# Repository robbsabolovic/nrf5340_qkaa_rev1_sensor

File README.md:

# nrf5340_qkaa_rev1_sensor
Simple Kicad 6.0 nRF5340 sensor board example

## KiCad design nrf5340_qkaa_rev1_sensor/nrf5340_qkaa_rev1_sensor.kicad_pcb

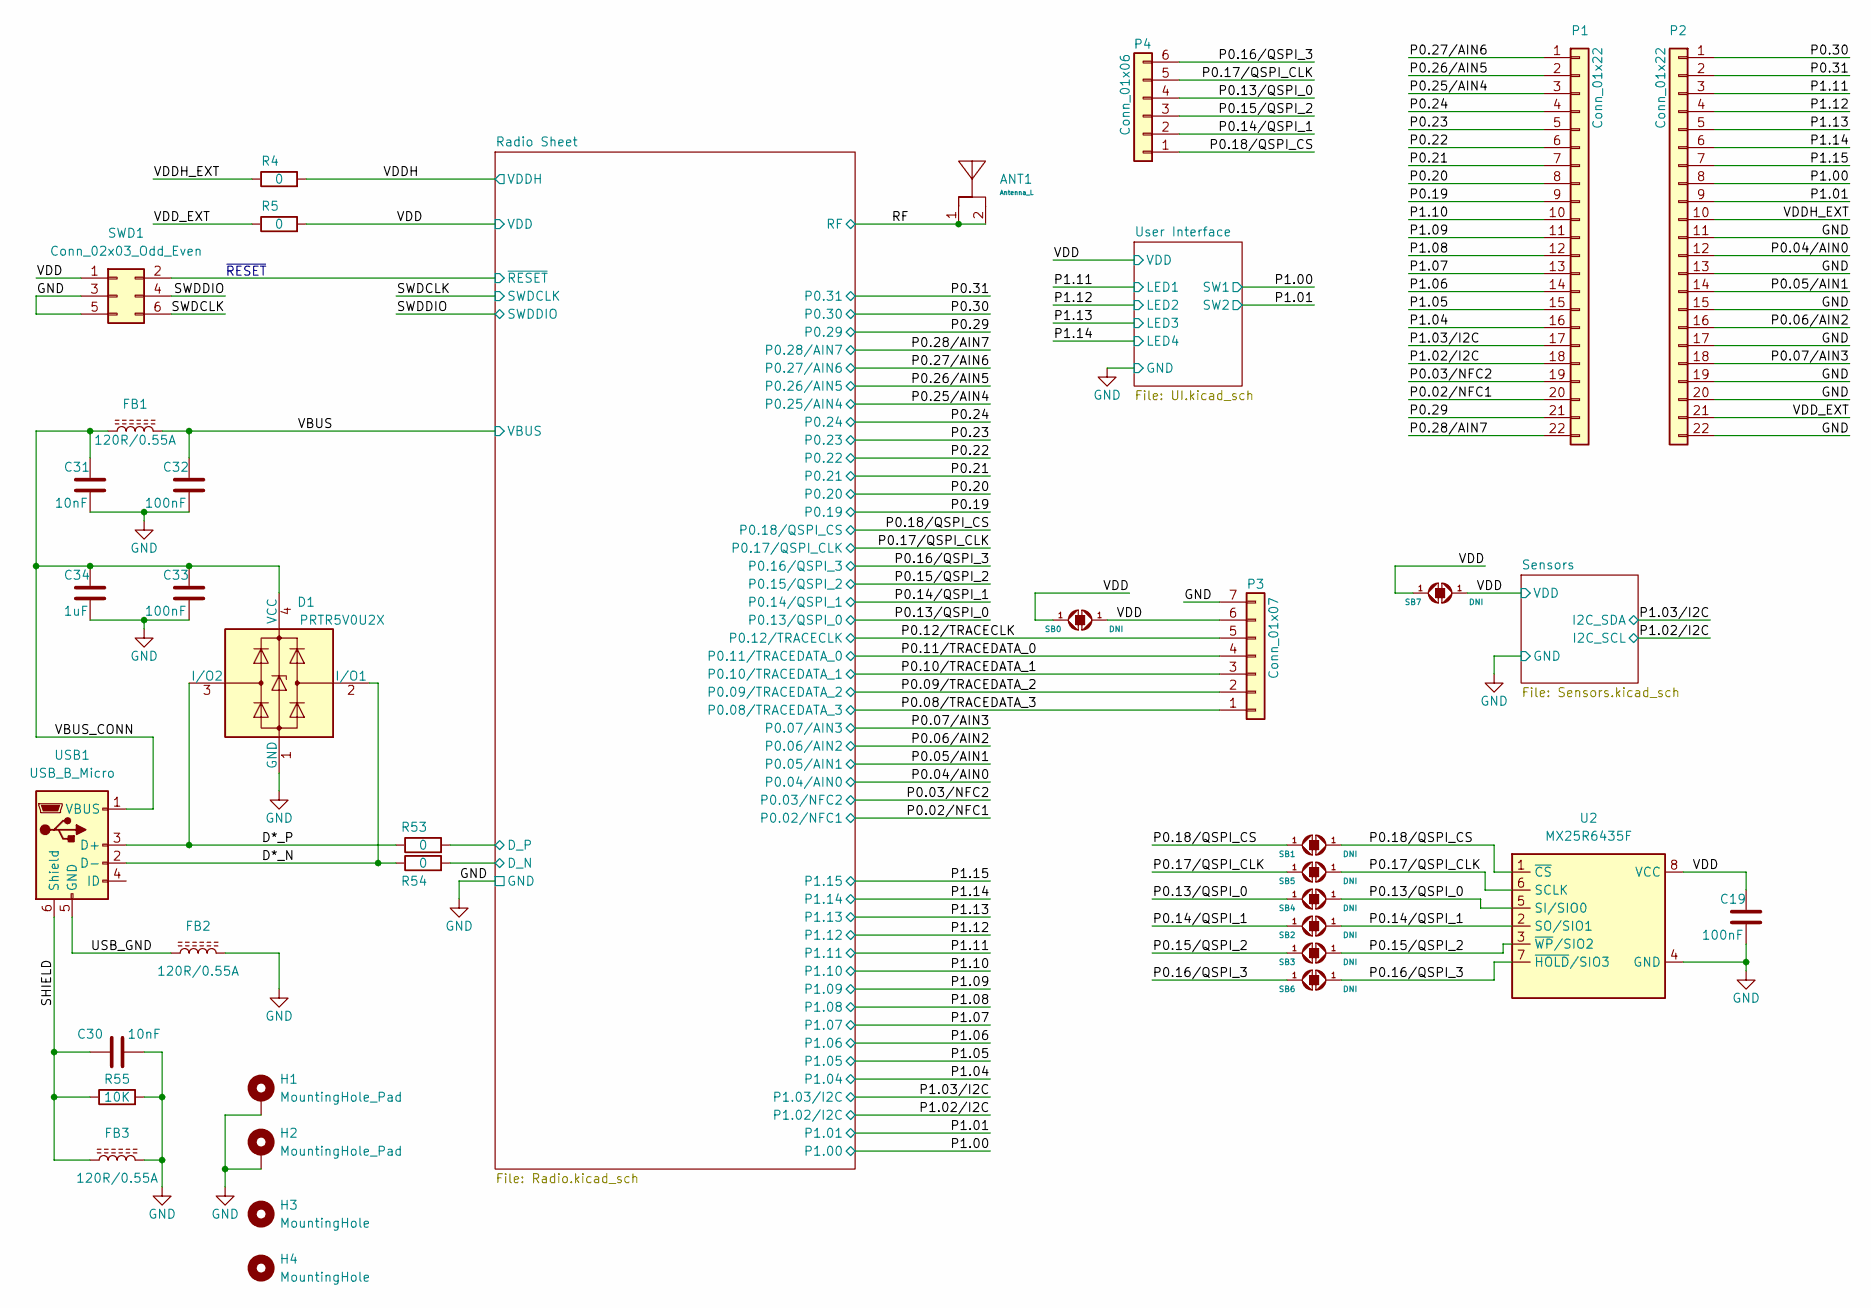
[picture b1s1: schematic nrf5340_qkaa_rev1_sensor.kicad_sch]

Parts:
ANT1: Antenna_L; ANTENNA_L_2_4GHZ
C19, C32, C33: 100nF; C_0201
C30, C31: 10nF; C_0201
C34: 1uF; C_0603
D1: PRTR5V0U2X; SOT-143
FB1, FB2, FB3: 120R/0.55A; FB_0603
H1, H2: MountingHole_Pad; MountingHole_2.5mm_Plated
H3, H4: MountingHole; MountingHole_2.5mm
P1, P2: Conn_01x22; PinHeader_1x022_P2.54mm_Vertical
P3: Conn_01x07; PinHeader_1x07_P2.54mm_Vertical
P4: Conn_01x06; PinHeader_1x06_P2.54mm_Vertical
R4, R5, R53, R54: 0; R_0201
R55: 10K; R_0201
SB0, SB1, SB2, SB3, SB4, SB5, SB6, SB7: DNI; SB_PAD_SHORT
SWD1: Conn_02x03_Odd_Even; TC2030-IDC-NL
U2: MX25R6435F; SOP-8_3.9x4.9mm_P1.27mm
USB1: USB_B_Micro; USB_Micro-B_Amphenol_10103594-0001LF_Horizontal

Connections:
/D*_N: D1.2 (I/O1), R54.1, USB1.2 (D-)
/D*_P: D1.3 (I/O2), R53.1, USB1.3 (D+)
/P0.02/NFC1: P1.20; also elsewhere on the board
/P0.03/NFC2: P1.19; also elsewhere on the board
/P0.04/AIN0: P2.12; also elsewhere on the board
/P0.05/AIN1: P2.14; also elsewhere on the board
/P0.06/AIN2: P2.16; also elsewhere on the board
/P0.07/AIN3: P2.18; also elsewhere on the board
/P0.08/TRACEDATA_3: P3.1; also elsewhere on the board
/P0.09/TRACEDATA_2: P3.2; also elsewhere on the board
/P0.10/TRACEDATA_1: P3.3; also elsewhere on the board
/P0.11/TRACEDATA_0: P3.4; also elsewhere on the board
/P0.12/TRACECLK: P3.5; also elsewhere on the board
/P0.13/QSPI_0: P4.4, SB4.1, U2.5 (SI/SIO0); also elsewhere on the board
/P0.14/QSPI_1: P4.2, SB2.1, U2.2 (SO/SIO1); also elsewhere on the board
/P0.15/QSPI_2: P4.3, SB3.1, U2.3 (~WP/SIO2); also elsewhere on the board
/P0.16/QSPI_3: P4.6, SB6.1, U2.7 (~HOLD/SIO3); also elsewhere on the board
/P0.17/QSPI_CLK: P4.5, SB5.1, U2.6 (SCLK); also elsewhere on the board
/P0.18/QSPI_CS: P4.1, SB1.1, U2.1 (~CS); also elsewhere on the board
/P0.19: P1.9; also elsewhere on the board
/P0.20: P1.8; also elsewhere on the board
/P0.21: P1.7; also elsewhere on the board
/P0.22: P1.6; also elsewhere on the board
/P0.23: P1.5; also elsewhere on the board
/P0.24: P1.4; also elsewhere on the board
/P0.25/AIN4: P1.3; also elsewhere on the board
/P0.26/AIN5: P1.2; also elsewhere on the board
/P0.27/AIN6: P1.1; also elsewhere on the board
/P0.28/AIN7: P1.22; also elsewhere on the board
/P0.29: P1.21; also elsewhere on the board
/P0.30: P2.1; also elsewhere on the board
/P0.31: P2.2; also elsewhere on the board
/P1.00: P2.8; also elsewhere on the board
/P1.01: P2.9; also elsewhere on the board
/P1.02/I2C: P1.18; also elsewhere on the board
/P1.03/I2C: P1.17; also elsewhere on the board
/P1.04: P1.16; also elsewhere on the board
/P1.05: P1.15; also elsewhere on the board
/P1.06: P1.14; also elsewhere on the board
/P1.07: P1.13; also elsewhere on the board
/P1.08: P1.12; also elsewhere on the board
/P1.09: P1.11; also elsewhere on the board
/P1.10: P1.10; also elsewhere on the board
/P1.11: P2.3; also elsewhere on the board
/P1.12: P2.4; also elsewhere on the board
/P1.13: P2.5; also elsewhere on the board
/P1.14: P2.6; also elsewhere on the board
/P1.15: P2.7; also elsewhere on the board
/RF: ANT1.1, ANT1.2; also elsewhere on the board
/Radio Sheet/D_N: R54.2; also elsewhere on the board
/Radio Sheet/D_P: R53.2; also elsewhere on the board
/Radio Sheet/~RESET: SWD1.2; also elsewhere on the board
/SHIELD: C30.1, FB3.1, R55.1, USB1.6 (Shield)
/SWDCLK: SWD1.6; also elsewhere on the board
/SWDDIO: SWD1.4; also elsewhere on the board
/USB_GND: FB2.1, USB1.5 (GND)
/VBUS_CONN: C31.1, C33.1, C34.1, D1.4 (VCC), FB1.1, USB1.1 (VBUS)
/VDDH: R4.2; also elsewhere on the board
/VDDH_EXT: P2.10, R4.1
/VDD_EXT: P2.21, R5.1
GND: C19.2, C30.2, C31.2, C32.2, C33.2, C34.2, D1.1 (GND), FB2.2, FB3.2, H1.1, H2.1, P2.11, P2.13, P2.15, P2.17, P2.19, P2.20, P2.22, P3.7, R55.2, SWD1.3, SWD1.5, U2.4 (GND); also elsewhere on the board
VBUS: C32.1, FB1.2; also elsewhere on the board
VDD: C19.1, P3.6, R5.2, SB0.1, SB7.1, SWD1.1, U2.8 (VCC); also elsewhere on the board

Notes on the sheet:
~{RESET}

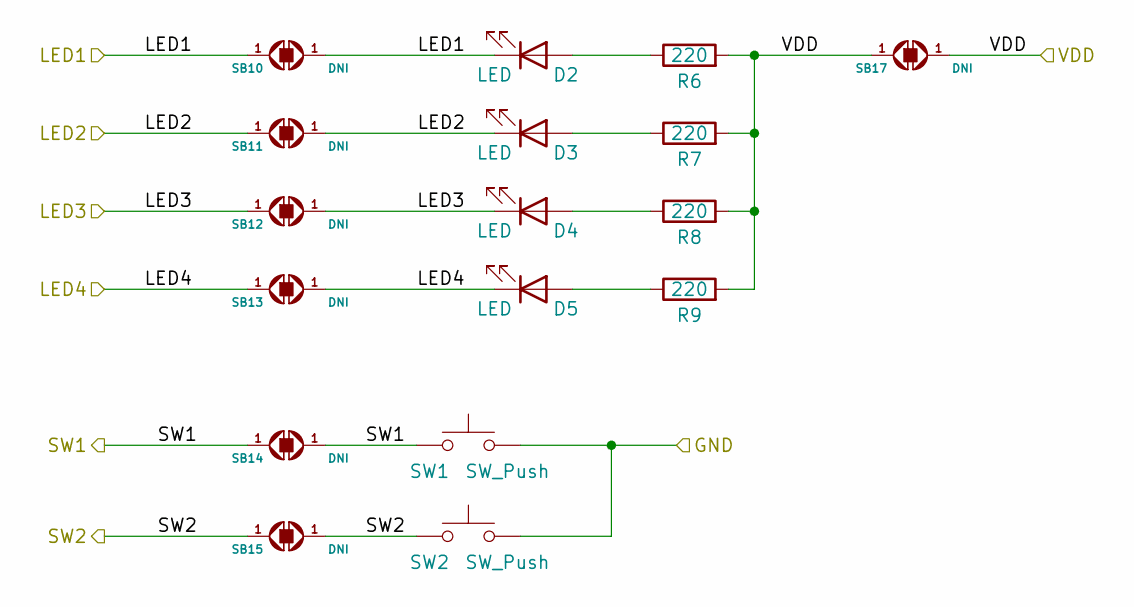
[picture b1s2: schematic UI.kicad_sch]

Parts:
D2, D3, D4, D5: LED; LED_0603_1608Metric
R6, R7, R8, R9: 220; R_0402
SB10, SB11, SB12, SB13, SB14, SB15, SB17: DNI; SB_PAD_SHORT
SW1, SW2: SW_Push; Panasonic_EVQPUK_EVQPUB

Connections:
/P1.00: SB14.1, SW1.1; also elsewhere on the board
/P1.01: SB15.1, SW2.1; also elsewhere on the board
/P1.11: D2.1 (K), SB10.1; also elsewhere on the board
/P1.12: D3.1 (K), SB11.1; also elsewhere on the board
/P1.13: D4.1 (K), SB12.1; also elsewhere on the board
/P1.14: D5.1 (K), SB13.1; also elsewhere on the board
GND: SW1.2, SW2.2; also elsewhere on the board
unnamed: D2.2 (A), R6.1
unnamed: D3.2 (A), R7.1
unnamed: D4.2 (A), R8.1
unnamed: D5.2 (A), R9.1
VDD: R6.2, R7.2, R8.2, R9.2, SB17.1; also elsewhere on the board

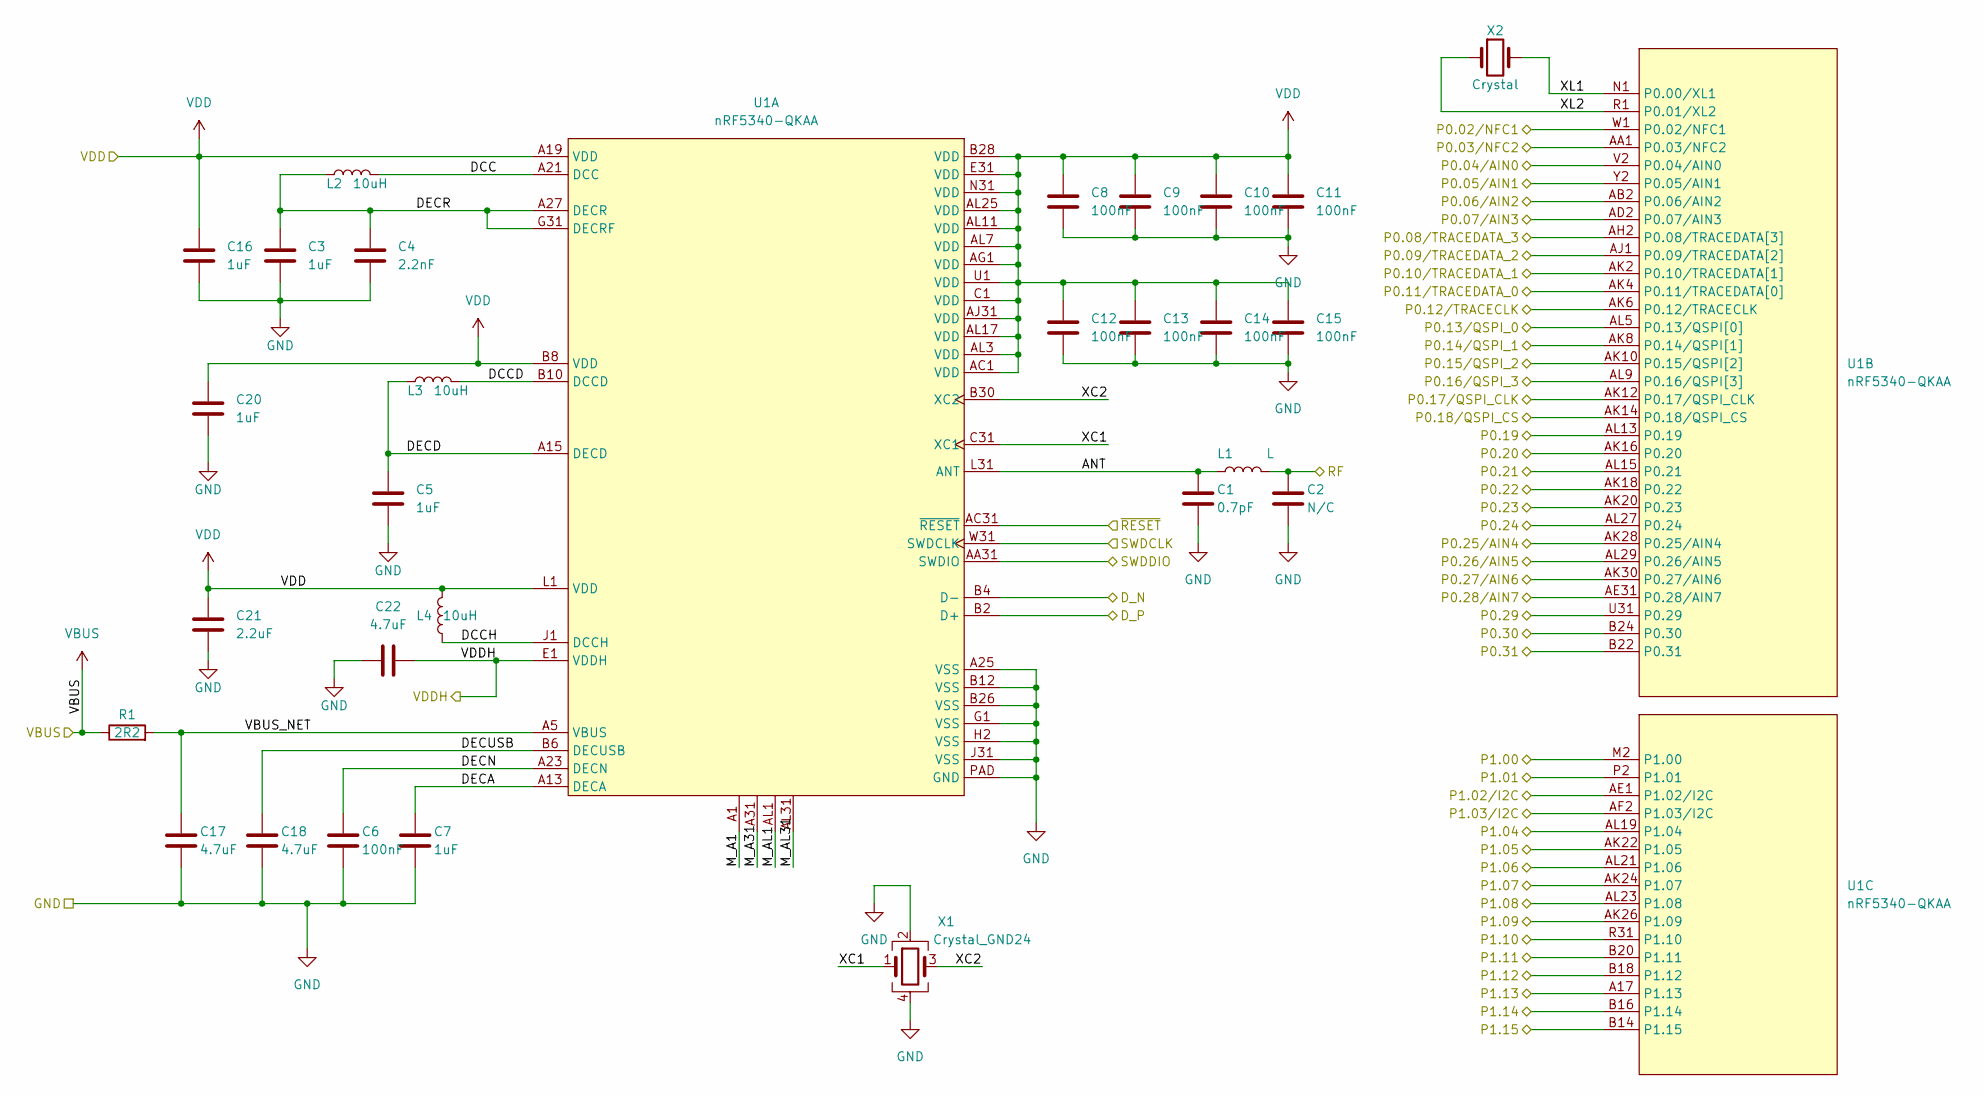
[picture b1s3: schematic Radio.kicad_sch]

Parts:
C1: 0.7pF; C_0201
C2: N/C; C_0201
C3, C5, C7, C16, C20: 1uF; C_0402
C4: 2.2nF; C_0201
C6, C8, C9, C10, C11, C12, C13, C14, C15: 100nF; C_0201
C17, C18, C22: 4.7uF; C_0603
C21: 2.2uF; C_0603
L1: L; L_0201
L2, L3, L4: 10uH; L_0603
R1: 2R2; R_0201
U1: nRF5340-QKAA; Nordic-AQFN-1EP_7x7mm_P0.4mm
X1: Crystal_GND24; XTAL_32M_4PIN
X2: Crystal; XTAL_32768Hz_2PIN

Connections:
/P0.02/NFC1: U1.W1 (P0.02/NFC1); also elsewhere on the board
/P0.03/NFC2: U1.AA1 (P0.03/NFC2); also elsewhere on the board
/P0.04/AIN0: U1.V2 (P0.04/AIN0); also elsewhere on the board
/P0.05/AIN1: U1.Y2 (P0.05/AIN1); also elsewhere on the board
/P0.06/AIN2: U1.AB2 (P0.06/AIN2); also elsewhere on the board
/P0.07/AIN3: U1.AD2 (P0.07/AIN3); also elsewhere on the board
/P0.08/TRACEDATA_3: U1.AH2 (P0.08/TRACEDATA[3]); also elsewhere on the board
/P0.09/TRACEDATA_2: U1.AJ1 (P0.09/TRACEDATA[2]); also elsewhere on the board
/P0.10/TRACEDATA_1: U1.AK2 (P0.10/TRACEDATA[1]); also elsewhere on the board
/P0.11/TRACEDATA_0: U1.AK4 (P0.11/TRACEDATA[0]); also elsewhere on the board
/P0.12/TRACECLK: U1.AK6 (P0.12/TRACECLK); also elsewhere on the board
/P0.13/QSPI_0: U1.AL5 (P0.13/QSPI[0]); also elsewhere on the board
/P0.14/QSPI_1: U1.AK8 (P0.14/QSPI[1]); also elsewhere on the board
/P0.15/QSPI_2: U1.AK10 (P0.15/QSPI[2]); also elsewhere on the board
/P0.16/QSPI_3: U1.AL9 (P0.16/QSPI[3]); also elsewhere on the board
/P0.17/QSPI_CLK: U1.AK12 (P0.17/QSPI_CLK); also elsewhere on the board
/P0.18/QSPI_CS: U1.AK14 (P0.18/QSPI_CS); also elsewhere on the board
/P0.19: U1.AL13 (P0.19); also elsewhere on the board
/P0.20: U1.AK16 (P0.20); also elsewhere on the board
/P0.21: U1.AL15 (P0.21); also elsewhere on the board
/P0.22: U1.AK18 (P0.22); also elsewhere on the board
/P0.23: U1.AK20 (P0.23); also elsewhere on the board
/P0.24: U1.AL27 (P0.24); also elsewhere on the board
/P0.25/AIN4: U1.AK28 (P0.25/AIN4); also elsewhere on the board
/P0.26/AIN5: U1.AL29 (P0.26/AIN5); also elsewhere on the board
/P0.27/AIN6: U1.AK30 (P0.27/AIN6); also elsewhere on the board
/P0.28/AIN7: U1.AE31 (P0.28/AIN7); also elsewhere on the board
/P0.29: U1.U31 (P0.29); also elsewhere on the board
/P0.30: U1.B24 (P0.30); also elsewhere on the board
/P0.31: U1.B22 (P0.31); also elsewhere on the board
/P1.00: U1.M2 (P1.00); also elsewhere on the board
/P1.01: U1.P2 (P1.01); also elsewhere on the board
/P1.02/I2C: U1.AE1 (P1.02/I2C); also elsewhere on the board
/P1.03/I2C: U1.AF2 (P1.03/I2C); also elsewhere on the board
/P1.04: U1.AL19 (P1.04); also elsewhere on the board
/P1.05: U1.AK22 (P1.05); also elsewhere on the board
/P1.06: U1.AL21 (P1.06); also elsewhere on the board
/P1.07: U1.AK24 (P1.07); also elsewhere on the board
/P1.08: U1.AL23 (P1.08); also elsewhere on the board
/P1.09: U1.AK26 (P1.09); also elsewhere on the board
/P1.10: U1.R31 (P1.10); also elsewhere on the board
/P1.11: U1.B20 (P1.11); also elsewhere on the board
/P1.12: U1.B18 (P1.12); also elsewhere on the board
/P1.13: U1.A17 (P1.13); also elsewhere on the board
/P1.14: U1.B16 (P1.14); also elsewhere on the board
/P1.15: U1.B14 (P1.15); also elsewhere on the board
/RF: C2.1, L1.2; also elsewhere on the board
/Radio Sheet/ANT: C1.1, L1.1, U1.L31 (ANT)
/Radio Sheet/DCC: L2.2, U1.A21 (DCC)
/Radio Sheet/DCCD: L3.2, U1.B10 (DCCD)
/Radio Sheet/DCCH: L4.1, U1.J1 (DCCH)
/Radio Sheet/DECA: C7.1, U1.A13 (DECA)
/Radio Sheet/DECD: C5.1, L3.1, U1.A15 (DECD)
/Radio Sheet/DECN: C6.1, U1.A23 (DECN)
/Radio Sheet/DECR: C3.1, C4.1, L2.1, U1.A27 (DECR), U1.G31 (DECRF)
/Radio Sheet/DECUSB: C18.1, U1.B6 (DECUSB)
/Radio Sheet/D_N: U1.B4 (D-); also elsewhere on the board
/Radio Sheet/D_P: U1.B2 (D+); also elsewhere on the board
/Radio Sheet/M_A1: U1.A1
/Radio Sheet/M_A31: U1.A31
/Radio Sheet/M_AL1: U1.AL1
/Radio Sheet/M_AL31: U1.AL31
/Radio Sheet/VBUS_NET: C17.1, R1.2, U1.A5 (VBUS)
/Radio Sheet/XC1: U1.C31 (XC1), X1.1
/Radio Sheet/XC2: U1.B30 (XC2), X1.3
/Radio Sheet/XL1: U1.N1 (P0.00/XL1), X2.2
/Radio Sheet/XL2: U1.R1 (P0.01/XL2), X2.1
/Radio Sheet/~RESET: U1.AC31 (~RESET); also elsewhere on the board
/SWDCLK: U1.W31 (SWDCLK); also elsewhere on the board
/SWDDIO: U1.AA31 (SWDIO); also elsewhere on the board
/VDDH: C22.1, U1.E1 (VDDH); also elsewhere on the board
GND: C1.2, C2.2, C3.2, C4.2, C5.2, C6.2, C7.2, C8.2, C9.2, C10.2, C11.2, C12.2, C13.2, C14.2, C15.2, C16.2, C17.2, C18.2, C20.2, C21.2, C22.2, U1.A25 (VSS), U1.B12 (VSS), U1.B26 (VSS), U1.G1 (VSS), U1.H2 (VSS), U1.J31 (VSS), U1.PAD (GND), X1.2, X1.4; also elsewhere on the board
VBUS: R1.1; also elsewhere on the board
VDD: C8.1, C9.1, C10.1, C11.1, C12.1, C13.1, C14.1, C15.1, C16.1, C20.1, C21.1, L4.2, U1.A19 (VDD), U1.AC1 (VDD), U1.AG1 (VDD), U1.AJ31 (VDD), U1.AL3 (VDD), U1.AL7 (VDD), U1.AL11 (VDD), U1.AL17 (VDD), U1.AL25 (VDD), U1.B8 (VDD), U1.B28 (VDD), U1.C1 (VDD), U1.E31 (VDD), U1.L1 (VDD), U1.N31 (VDD), U1.U1 (VDD); also elsewhere on the board

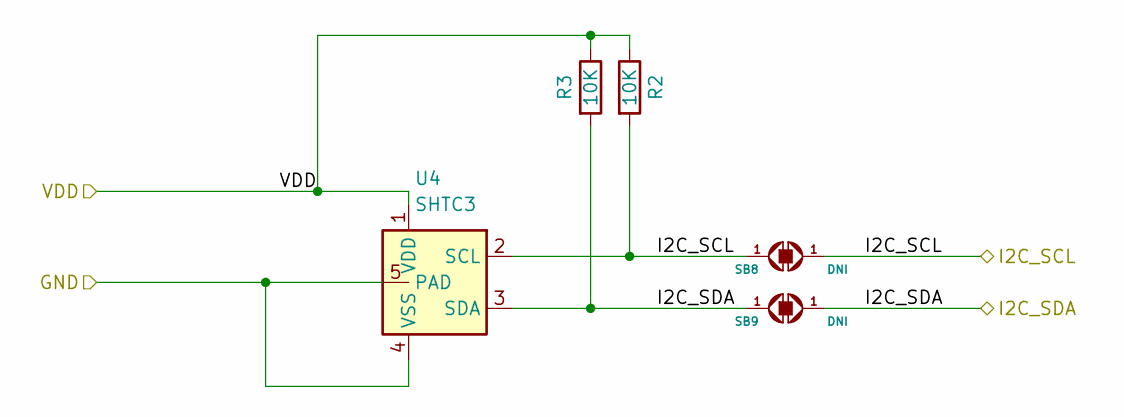
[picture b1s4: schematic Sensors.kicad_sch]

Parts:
R2, R3: 10K; R_0201
SB8, SB9: DNI; SB_PAD_SHORT
U4: SHTC3; Sensirion_DFN-4-1EP_2x2mm_P1mm_EP0.7x1.6mm

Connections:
/P1.02/I2C: R2.2, SB8.1, U4.2 (SCL); also elsewhere on the board
/P1.03/I2C: R3.2, SB9.1, U4.3 (SDA); also elsewhere on the board
GND: U4.4 (VSS), U4.5 (PAD); also elsewhere on the board
VDD: R2.1, R3.1, U4.1 (VDD); also elsewhere on the board

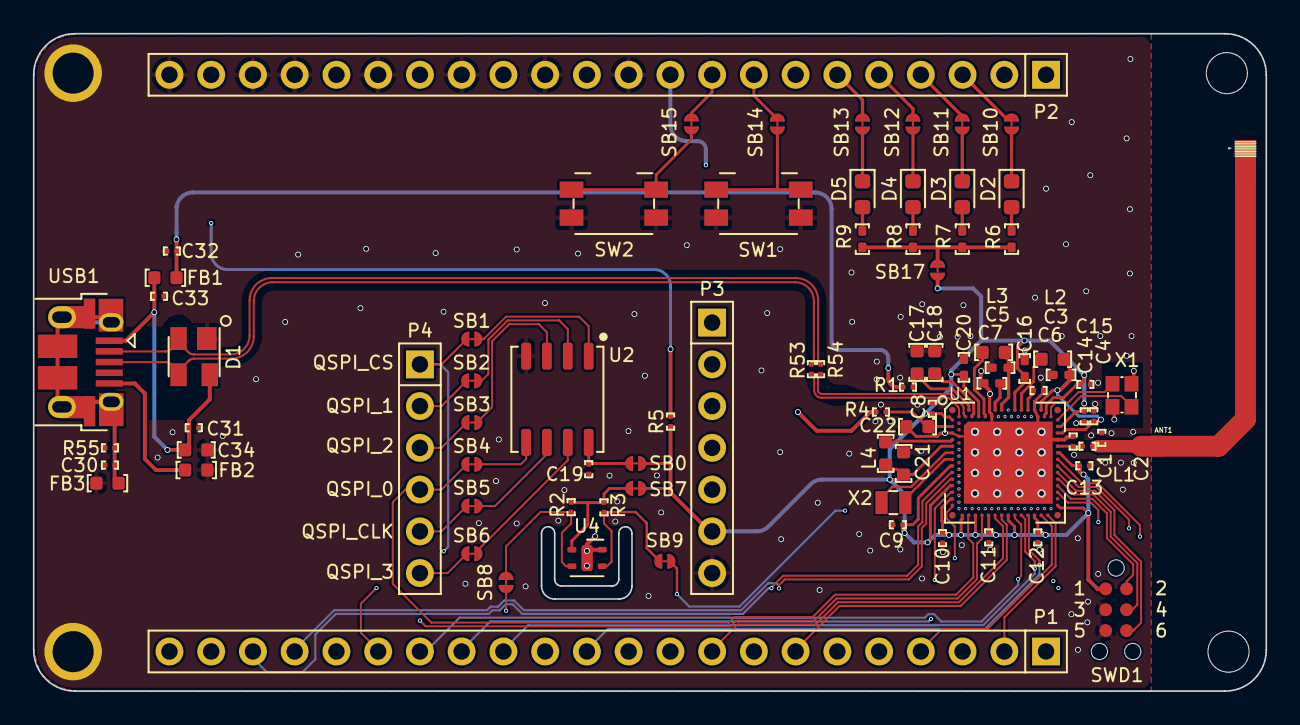
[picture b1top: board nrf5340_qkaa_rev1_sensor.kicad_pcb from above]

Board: 4 copper layers, 75.0 x 40.0 mm, 86 parts (0 on the bottom side), 81 nets.

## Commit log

2022-01-25 Add files via upload
    Initial release of nRF5340 example design project
2022-01-25 Add files via upload
    nRF5340 example layout with temp/humidity sensor, external flash memory, USB connection, and simple button/led user interface.
